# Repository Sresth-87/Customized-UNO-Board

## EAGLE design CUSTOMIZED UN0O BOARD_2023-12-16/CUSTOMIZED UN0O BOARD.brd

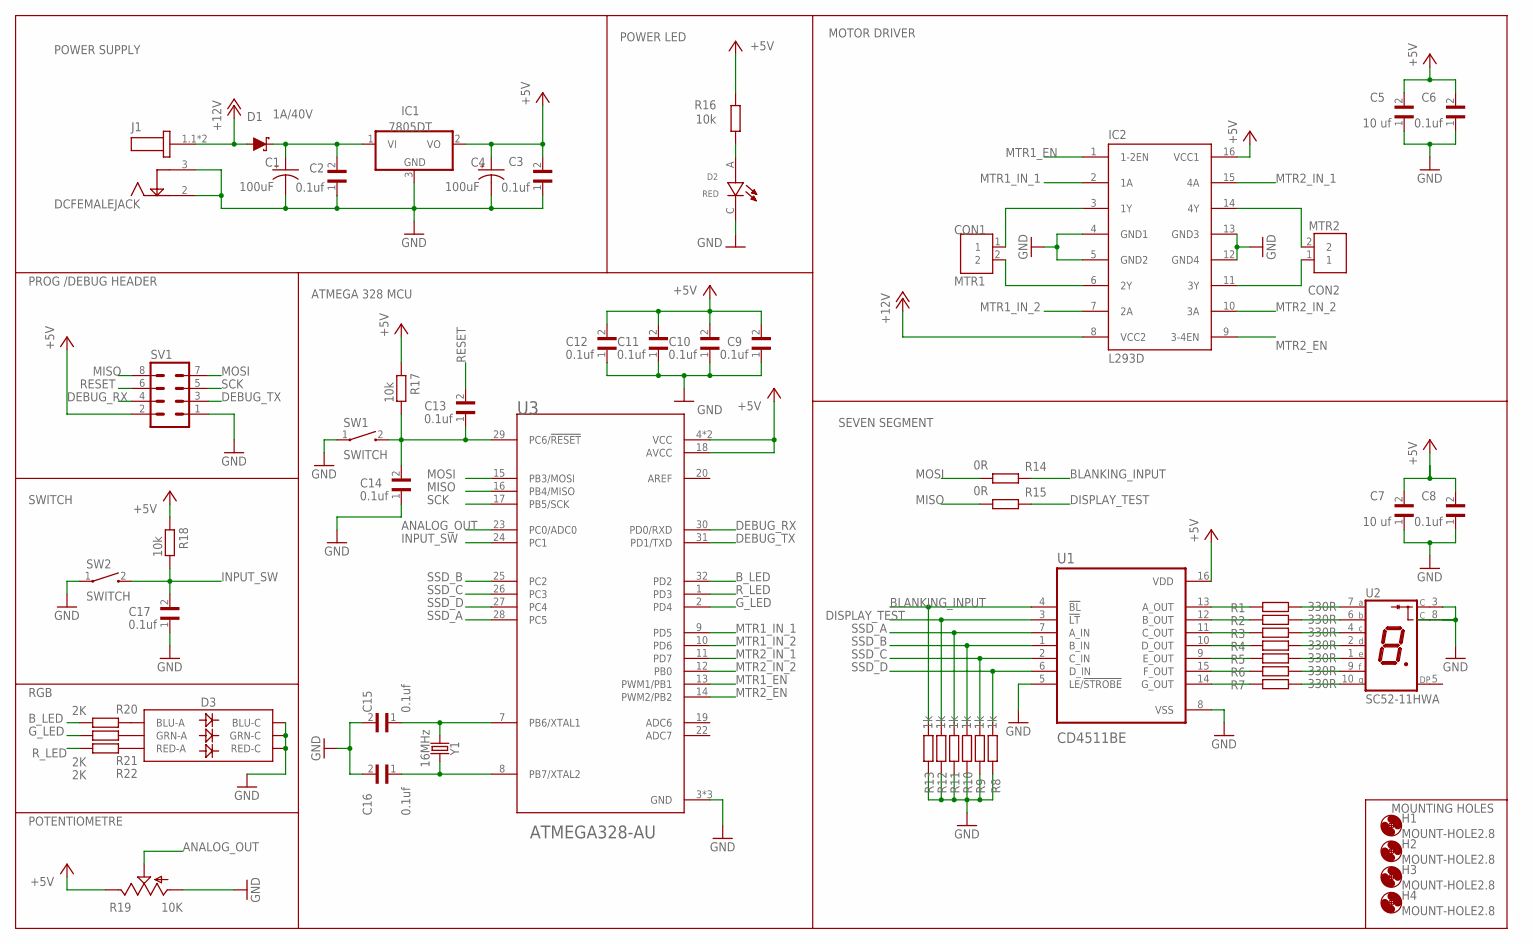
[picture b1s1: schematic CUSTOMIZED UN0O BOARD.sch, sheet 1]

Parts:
C1, C4: 100uF; CPOL-RADIAL-2.5MM-6.5MM
C2, C3, C5, C6, C7, C8, C9, C10, C11, C12, C13, C14, C15, C17: CAPACITOR; C0603
C16: 22pf; C0603
D1: 3A/40V/500mV; SMA-DIODE
D2: RED; LEDC1608X65N
D3: LED-RGBNO_IC; LED-TRICOLOR-5050
H1, H2, H3, H4: MOUNT-HOLE2.8; 2,8
IC1: 7806DT; TO252
IC2: L293D; DIL16
J1: DCJ200-05-A-XX-X_REVA; GCT_DCJ200-05-A-XX-X_REVA
J2, J3: 282836-2; CONN_282836-2
R1, R2, R3, R4, R5, R6, R7: 330R; R0603
R8, R9, R10, R11, R12, R13: 1k; R0603
R14, R15: 0R; R0603
R16, R17, R18: 10k; R0603
R19: 10K; S64W
R20, R21, R22: 2K; R0603
SV1: MA04-2
SW1, SW2: SWITCH; SW_1437566-3
U1: CD4511BE; DIP794W45P254L1969H508Q16
U2: SC52-11HWA; LED_SC52-11HWA
U3: ATMEGA328-AU; QFP80P900X900X120-32N
Y1: 16MHz; HC49US

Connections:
+5V: C3.2, C4.1 (+), C5.2, C6.2, C7.2, C8.2, C9.2, C10.2, C11.2, C12.2, IC1.2 (VO), IC2.16 (VCC1), R16.2, R17.2, R18.2, R19.E, SV1.2, U1.16 (VDD), U3.4 (VCC), U3.6 (VCC), U3.18 (AVCC)
+12V: D1.A, IC2.8 (VCC2), J1.1.1 (1), J1.1.2 (1)
ANALOG_OUT: R19.S, U3.23 (PC0/ADC0)
BLANKING_INPUT: R13.2, R14.2, U1.4 (!BL)
B_LED: R20.2, U3.32 (PD2)
DEBUG_RX: SV1.4, U3.30 (PD0/RXD)
DEBUG_TX: SV1.3, U3.31 (PD1/TXD)
DISPLAY_TEST: R12.2, R15.2, U1.3 (!LT)
GND: C1.2 (-), C2.1, C3.1, C4.2 (-), C5.1, C6.1, C7.1, C8.1, C9.1, C10.1, C11.1, C12.1, C14.1, C15.2, C16.2, C17.1, D2.C, D3.4 (BLU-C), D3.5 (RED-C), D3.6 (GRN-C), IC1.3 (GND), IC2.4 (GND1), IC2.5 (GND2), IC2.12 (GND4), IC2.13 (GND3), J1.2, J1.3, R8.1, R9.1, R10.1, R11.1, R12.1, R13.1, R19.A, SV1.1, SW1.1, SW2.1, U1.5 (LE/!STROBE), U1.8 (VSS), U2.3 (C), U2.8 (C), U3.3 (GND), U3.5 (GND), U3.21 (GND)
G_LED: R21.2, U3.2 (PD4)
INPUT_SW: C17.2, R18.1, SW2.2, U3.24 (PC1)
MISO: R15.1, SV1.8, U3.16 (PB4/MISO)
MOSI: R14.1, SV1.7, U3.15 (PB3/MOSI)
MTR1_EN: IC2.1 (1-2EN), U3.13 (PWM1/PB1)
MTR1_IN_1: IC2.2 (1A), U3.9 (PD5)
MTR1_IN_2: IC2.7 (2A), U3.10 (PD6)
MTR2_EN: IC2.9 (3-4EN), U3.14 (PWM2/PB2)
MTR2_IN_1: IC2.15 (4A), U3.11 (PD7)
MTR2_IN_2: IC2.10 (3A), U3.12 (PB0)
unnamed: D2.A, R16.1
unnamed: IC2.6 (2Y), J2.2
unnamed: C1.1 (+), C2.2, D1.C, IC1.1 (VI)
unnamed: IC2.3 (1Y), J2.1
unnamed: IC2.14 (4Y), J3.2
unnamed: IC2.11 (3Y), J3.1
unnamed: R5.1, U1.9 (E_OUT)
unnamed: D3.3 (BLU-A), R20.1
unnamed: D3.1 (GRN-A), R21.1
unnamed: R5.2, U2.1 (E)
unnamed: R1.1, U1.13 (A_OUT)
unnamed: D3.2 (RED-A), R22.1
unnamed: R2.1, U1.12 (B_OUT)
unnamed: R3.1, U1.11 (C_OUT)
unnamed: R4.1, U1.10 (D_OUT)
unnamed: R6.1, U1.15 (F_OUT)
unnamed: R7.1, U1.14 (G_OUT)
unnamed: C13.1, C14.2, R17.1, SW1.2, U3.29 (PC6/!RESET)
unnamed: R1.2, U2.7 (A)
unnamed: R2.2, U2.6 (B)
unnamed: R3.2, U2.4 (C)
unnamed: R4.2, U2.2 (D)
unnamed: R6.2, U2.9 (F)
unnamed: R7.2, U2.10 (G)
unnamed: C15.1, U3.7 (PB6/XTAL1), Y1.1
unnamed: C16.1, U3.8 (PB7/XTAL2), Y1.2
RESET: C13.2, SV1.6
R_LED: R22.2, U3.1 (PD3)
SCK: SV1.5, U3.17 (PB5/SCK)
SSD_A: R11.2, U1.7 (A_IN), U3.28 (PC5)
SSD_B: R10.2, U1.1 (B_IN), U3.25 (PC2)
SSD_C: R9.2, U1.2 (C_IN), U3.26 (PC3)
SSD_D: R8.2, U1.6 (D_IN), U3.27 (PC4)

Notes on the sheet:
MOTOR DRIVER
POWER SUPPLY
ATMEGA 328 MCU
SEVEN SEGMENT
POWER LED
MOUNTING HOLES
PROG /DEBUG HEADER
SWITCH
RGB
POTENTIOMETRE

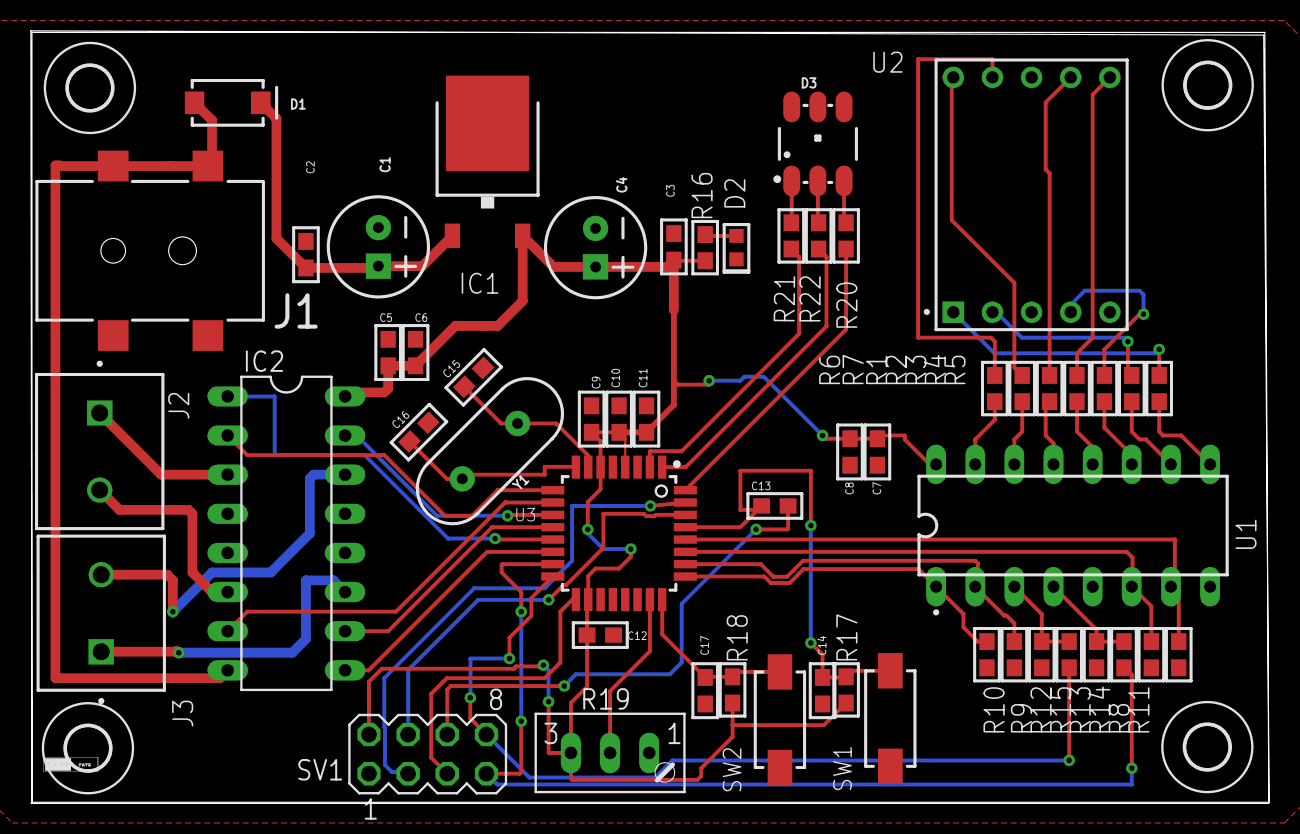
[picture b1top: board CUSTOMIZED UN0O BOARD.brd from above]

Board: 2 copper layers, 80.4 x 50.1 mm, 58 parts (0 on the bottom side), 52 nets.
